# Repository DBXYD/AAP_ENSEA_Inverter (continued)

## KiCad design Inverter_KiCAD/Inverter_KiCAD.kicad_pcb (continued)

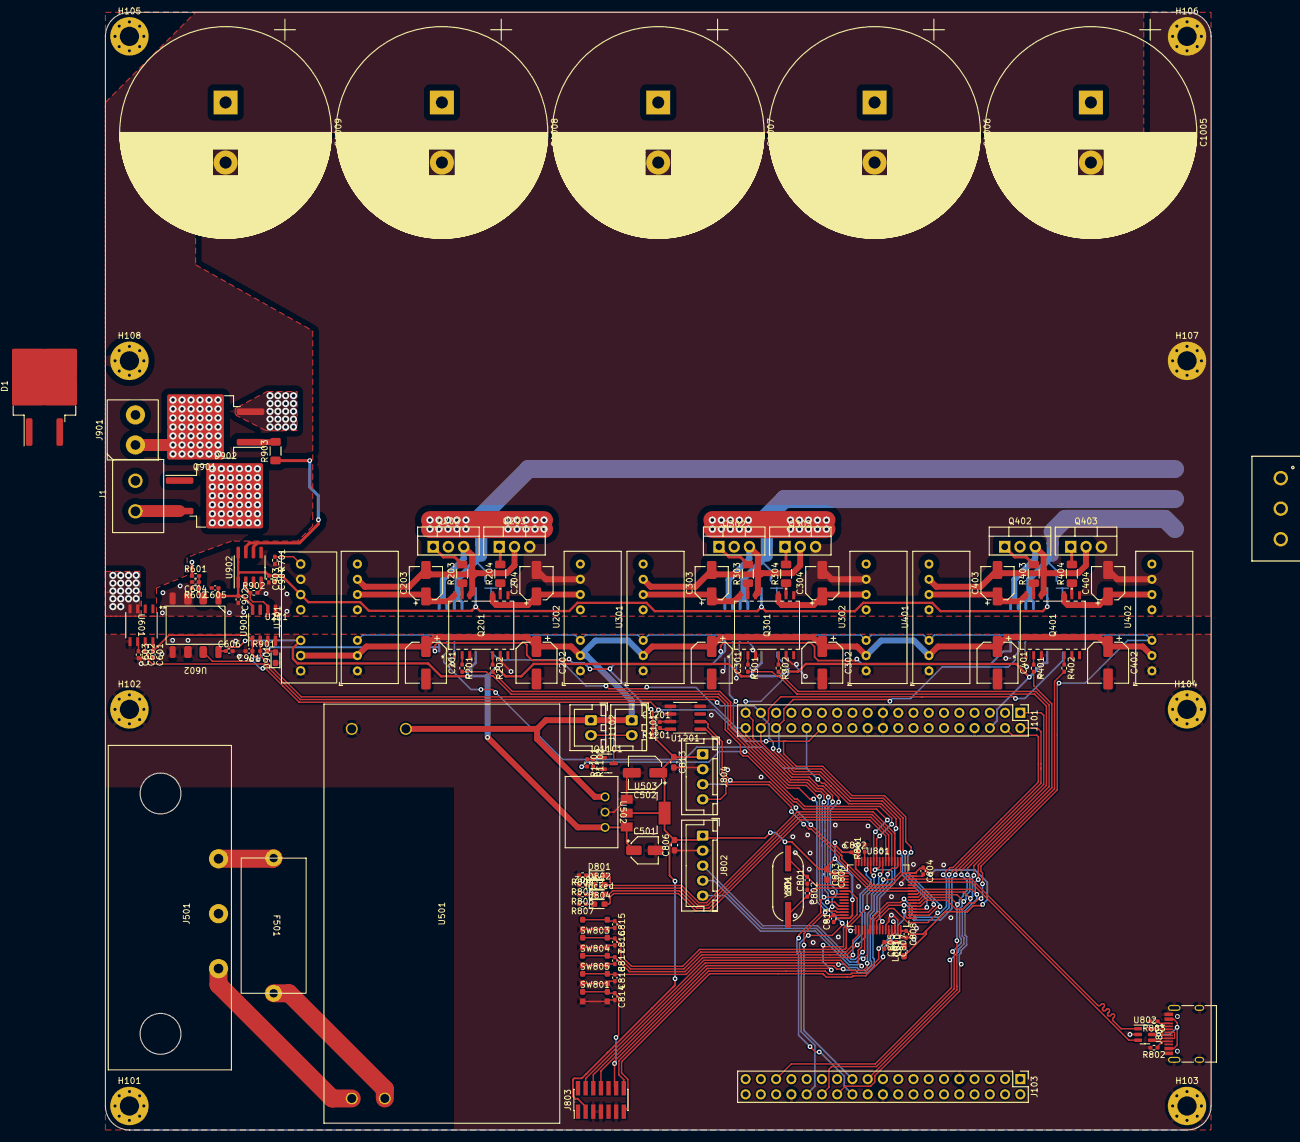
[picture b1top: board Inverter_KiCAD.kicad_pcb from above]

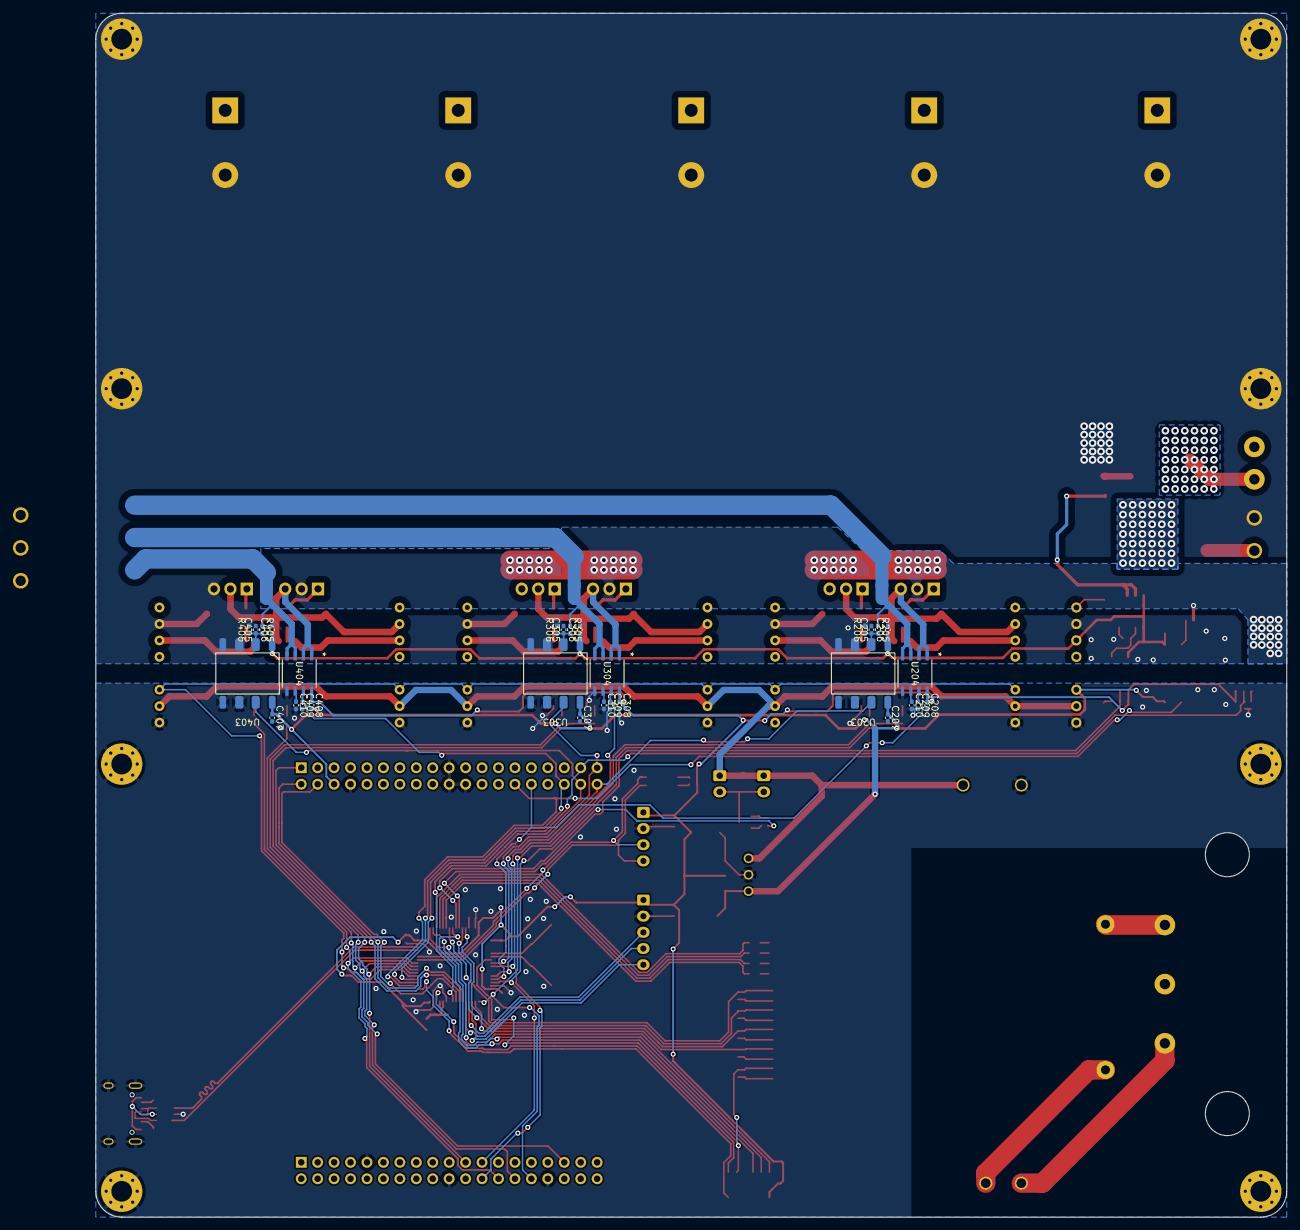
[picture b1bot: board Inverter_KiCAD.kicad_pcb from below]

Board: 4 copper layers, 184.0 x 186.0 mm, 169 parts (30 on the bottom side), 113 nets.

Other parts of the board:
locked: LED; LED_0603_1608Metric_Pad1.05x0.95mm_HandSolder

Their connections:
/MCU_STM32G474/USR_LED_3: locked.2 (A); also elsewhere on the board
unnamed 122: locked.1 (K); also elsewhere on the board

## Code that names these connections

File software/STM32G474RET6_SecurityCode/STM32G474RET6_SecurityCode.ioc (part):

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Mcu.Name=STM32G474R(B-C-E)Tx
Mcu.Package=LQFP64
Mcu.UserName=STM32G474RETx
PA0.Mode=IN1-Single-Ended
PA0.Signal=ADC1_IN1
PA1.Mode=IN2-Single-Ended
PA1.Signal=ADC1_IN2
PA11.Mode=Device
PA11.Signal=USB_DM
PA12.Mode=Device
PA12.Signal=USB_DP
PA13.Mode=Trace_Asynchronous_SW
PA13.Signal=SYS_JTMS-SWDIO
PA14.Mode=Trace_Asynchronous_SW
PA14.Signal=SYS_JTCK-SWCLK
PA15.GPIOParameters=GPIO_Label
PA15.GPIO_Label=USR_LED_4
PA15.Signal=GPIO_Output
PA2.Signal=S_TIM15_CH1
PA3.Signal=S_TIM15_CH2
PA4.GPIOParameters=GPIO_PuPd,GPIO_Label,GPIO_ModeDefaultEXTI
PA4.GPIO_Label=USR_BTN_2
PA4.GPIO_ModeDefaultEXTI=GPIO_MODE_IT_FALLING
PA4.GPIO_PuPd=GPIO_PULLUP
PA4.Signal=GPXTI4
PA5.GPIOParameters=GPIO_Label
PA5.GPIO_Label=ENC_BTN
PA5.Signal=GPXTI5
PA6.GPIOParameters=GPIO_Label
PA6.GPIO_Label=ENC_BTN_A
PA6.Signal=S_TIM3_CH1
PA7.GPIOParameters=GPIO_Label
PA7.GPIO_Label=ENC_BTN_B
PA7.Signal=S_TIM3_CH2
PA8.GPIOParameters=GPIO_Pu
PA8.GPIO_Pu=GPIO_PULLUP
PA8.Mode=I2C
PA8.Signal=I2C2_SDA
PA9.GPIOParameters=GPIO_Pu
PA9.GPIO_Pu=GPIO_PULLUP
PA9.Mode=I2C
PA9.Signal=I2C2_SCL
PB0.GPIOParameters=GPIO_Label
PB0.GPIO_Label=Nucleo_NRST
PB0.Signal=GPXTI0
PB1.Mode=IN1-Single-Ended
PB1.Signal=ADC3_IN1
PB10.Mode=Asynchronous
PB10.Signal=USART3_TX
PB11.Mode=Asynchronous
PB11.Signal=USART3_RX
PB12.Mode=IN3-Single-Ended
PB12.Signal=ADC4_IN3
PB13.Mode=IN5-Single-Ended
PB13.Signal=ADC3_IN5
PB14.Mode=IN4-Single-Ended
PB14.Signal=ADC4_IN4
PB2.Mode=IN12-Single-Ended
PB2.Signal=ADC2_IN12
PB3.Mode=Trace_Asynchronous_SW
PB3.Signal=SYS_JTDO-SWO
PB4.Signal=S_TIM16_CH1
PB5.GPIOParameters=GPIO_Label
PB5.GPIO_Label=ISO_PWM_BREAK
PB5.Signal=S_TIM17_CH1
PB6.GPIOParameters=GPIO_PuPd,GPIO_Label,GPIO_ModeDefaultEXTI
PB6.GPIO_Label=USR_BTN_3
PB6.GPIO_ModeDefaultEXTI=GPIO_MODE_IT_FALLING
PB6.GPIO_PuPd=GPIO_PULLUP
PB6.Signal=GPXTI6
PB7.GPIOParameters=GPIO_PuPd,GPIO_Label,GPIO_ModeDefaultEXTI
PB7.GPIO_Label=Soft_NRST
PB7.GPIO_ModeDefaultEXTI=GPIO_MODE_IT_FALLING
PB7.GPIO_PuPd=GPIO_PULLUP
PB7.Signal=GPXTI7
PC0.Signal=S_TIM1_CH1
PC1.Signal=S_TIM1_CH2
PC10.GPIOParameters=GPIO_Label
PC10.GPIO_Label=USR_LED_3
PC10.Signal=GPIO_Output
PC11.GPIOParameters=GPIO_Label
PC11.GPIO_Label=USR_LED_2
PC11.Signal=GPIO_Output
PC12.GPIOParameters=GPIO_Label
PC12.GPIO_Label=USR_LED_1
PC12.Signal=GPIO_Output
PC13.GPIOParameters=GPIO_Label
PC13.GPIO_Label=Pwr_Enable_U
PC13.Signal=GPIO_Output
PC14-OSC32_IN.GPIOParameters=GPIO_Label
PC14-OSC32_IN.GPIO_Label=Pwr_Enable_V
PC14-OSC32_IN.Signal=GPIO_Output
PC15-OSC32_OUT.GPIOParameters=GPIO_Label
PC15-OSC32_OUT.GPIO_Label=Pwr_Enable_W
PC15-OSC32_OUT.Signal=GPIO_Output
PC2.Signal=S_TIM1_CH3
PC3.Mode=IN9-Single-Ended
PC3.Signal=ADC2_IN9
PC4.Mode=Asynchronous
PC4.Signal=USART1_TX
PC5.Mode=Asynchronous
PC5.Signal=USART1_RX
PC6.Signal=S_TIM8_CH1
PC7.Signal=S_TIM8_CH2
PC8.Signal=S_TIM8_CH3
PC9.Signal=S_TIM8_CH4
PD2.GPIOParameters=GPIO_PuPd,GPIO_Label,GPIO_ModeDefaultEXTI
PD2.GPIO_Label=USR_BTN_1
PD2.GPIO_ModeDefaultEXTI=GPIO_MODE_IT_FALLING
PD2.GPIO_PuPd=GPIO_PULLUP
PD2.Signal=GPXTI2
PF0-OSC_IN.Mode=HSE-External-Oscillator
PF0-OSC_IN.Signal=RCC_OSC_IN
PF1-OSC_OUT.Mode=HSE-External-Oscillator
PF1-OSC_OUT.Signal=RCC_OSC_OUT
PG10-NRST.GPIOParameters=GPIO_PuPd,GPIO_Label
PG10-NRST.GPIO_Label=NRST
PG10-NRST.GPIO_PuPd=GPIO_PULLUP
PG10-NRST.Signal=GPIO_Input
RCC.HSE_VALUE=16000000
RCC.SYSCLKFreq_VALUE=170000000
RCC.SYSCLKSource=RCC_SYSCLKSOURCE_PLLCLK
board=custom

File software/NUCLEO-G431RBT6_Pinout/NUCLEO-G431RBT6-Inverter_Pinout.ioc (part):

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Mcu.Name=STM32G431R(6-8-B)Tx
Mcu.Package=LQFP64
Mcu.UserName=STM32G431RBTx
PA0.GPIOParameters=GPIO_Label
PA0.GPIO_Label=BUS_V
PA0.Mode=IN1-Single-Ended
PA0.Signal=ADC2_IN1
PA1.GPIOParameters=GPIO_Label
PA1.GPIO_Label=U_Imes
PA1.Mode=IN2-Single-Ended
PA1.Signal=ADC1_IN2
PA10.GPIOParameters=GPIO_Label
PA10.GPIO_Label=W_PWM_H
PA10.Signal=S_TIM1_CH3
PA13.GPIOParameters=GPIO_Label
PA13.GPIO_Label=T_SWDIO
PA13.Mode=Trace_Asynchronous_SW
PA13.Signal=SYS_JTMS-SWDIO
PA14.GPIOParameters=GPIO_Label
PA14.GPIO_Label=T_SWCLK
PA14.Mode=Trace_Asynchronous_SW
PA14.Signal=SYS_JTCK-SWCLK
PA2.Mode=Asynchronous
PA2.Signal=USART2_TX
PA3.Mode=Asynchronous
PA3.Signal=USART2_RX
PA4.Signal=S_TIM3_CH2
PA5.GPIOParameters=GPIO_Label
PA5.GPIO_Label=USR_LED
PA5.Signal=GPIO_Output
PA6.Signal=S_TIM3_CH1
PA8.GPIOParameters=GPIO_Label
PA8.GPIO_Label=U_PWM_H
PA8.Signal=S_TIM1_CH1
PA9.GPIOParameters=GPIO_Label
PA9.GPIO_Label=V_PWM_H
PA9.Signal=S_TIM1_CH2
PB0.GPIOParameters=GPIO_Label
PB0.GPIO_Label=W_Imes
PB0.Mode=IN15-Single-Ended
PB0.Signal=ADC1_IN15
PB1.GPIOParameters=GPIO_Label
PB1.GPIO_Label=V_Imes
PB1.Mode=IN12-Single-Ended
PB1.Signal=ADC1_IN12
PB13.GPIOParameters=GPIO_Label
PB13.GPIO_Label=U_PWM_L
PB13.Mode=PWM Generation1 CH1 CH1N
PB13.Signal=TIM1_CH1N
PB14.GPIOParameters=GPIO_Label
PB14.GPIO_Label=V_PWM_L
PB14.Mode=PWM Generation2 CH2 CH2N
PB14.Signal=TIM1_CH2N
PB15.GPIOParameters=GPIO_Label
PB15.GPIO_Label=W_PWM_L
PB15.Mode=PWM Generation3 CH3 CH3N
PB15.Signal=TIM1_CH3N
PB3.GPIOParameters=GPIO_Label
PB3.GPIO_Label=T_SWO
PB3.Mode=Trace_Asynchronous_SW
PB3.Signal=SYS_JTDO-SWO
PC0.GPIOParameters=GPIO_Label
PC0.GPIO_Label=U_VPh
PC0.Mode=IN6-Single-Ended
PC0.Signal=ADC2_IN6
PC1.GPIOParameters=GPIO_Label
PC1.GPIO_Label=W_VPh
PC1.Mode=IN7-Single-Ended
PC1.Signal=ADC2_IN7
PC10.Mode=Asynchronous
PC10.Signal=USART3_TX
PC11.Mode=Asynchronous
PC11.Signal=USART3_RX
PC13.GPIOParameters=GPIO_Label
PC13.GPIO_Label=USR_BTN
PC13.Signal=GPXTI13
PC14-OSC32_IN.Mode=LSE-External-Oscillator
PC14-OSC32_IN.Signal=RCC_OSC32_IN
PC15-OSC32_OUT.Mode=LSE-External-Oscillator
PC15-OSC32_OUT.Signal=RCC_OSC32_OUT
PC2.GPIOParameters=GPIO_Label
PC2.GPIO_Label=Bus_Imes
PC2.Mode=IN8-Single-Ended
PC2.Signal=ADC1_IN8
PC3.GPIOParameters=GPIO_Label
PC3.GPIO_Label=V_VPh
PC3.Mode=IN9-Single-Ended
PC3.Signal=ADC2_IN9
PC8.Signal=S_TIM3_CH3
PD2.GPIOParameters=GPIO_Label
PD2.GPIO_Label=NRST_SafetyUC
PD2.Signal=GPIO_Output
PF0-OSC_IN.Mode=HSE-External-Oscillator
PF0-OSC_IN.Signal=RCC_OSC_IN
PF1-OSC_OUT.Mode=HSE-External-Oscillator
PF1-OSC_OUT.Signal=RCC_OSC_OUT
RCC.HSE_VALUE=24000000
RCC.SYSCLKFreq_VALUE=170000000
RCC.SYSCLKSource=RCC_SYSCLKSOURCE_PLLCLK
board=NUCLEO-G431RB
boardIOC=true

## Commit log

2023-02-06 add folders and AAP presentation
2023-02-06 change git ignore
2023-02-06 Schema Architecture
2023-02-06 Update AAP
2023-02-14 change presentation, add datasheets
2023-02-14 change slides
2023-03-06 update slides AAP
2023-04-24 datasheets
2023-04-25 assigments footprints
2023-04-25 update schematic
2023-04-27 add project for mesuring deadtime
2023-04-27 add screen
2023-04-27 add break
2023-04-27 Ajouté(e) AAP_Inverter.drawio
2023-04-27 update ioc
2023-04-28 start schematic Nucleo board
2023-04-29 clear schematic errors
2023-05-01 end of sch, start pcb
2023-05-04 rooting done
2023-05-09 datasheet
2023-05-10 MAJ_AAP_Inverter.drawio
2023-05-10 update KiCAD 3D
2023-06-13 datasheet update
2023-06-13 change pcb
2023-06-13 apply changes
2023-06-27 Update KiCAD
2023-06-27 change pbs
2023-07-11 v0 PCB
2023-07-19 soldering done, start test, power supply ok
2023-08-01 update firmware
2023-08-28 fix version of kicad project
2023-08-28 update kicad project
2023-08-31 update pcb
2023-09-06 add command sheet
2023-09-06 add eve/ese components
2023-09-18 add G474RE base project
2023-09-19 add presentation final
2023-09-30 test on pcb v1
2023-09-30 add break code and enable output from buttons
2023-10-01 update security code
2023-10-01 add shell script for students
2023-10-09 update code
2023-11-06 change folders
2023-11-06 Added AAP_Inverter-Global.drawio.png
2023-11-06 add pictures
2023-11-06 resize jpg
